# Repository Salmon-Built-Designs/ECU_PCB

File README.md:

# ECU_PCB
PCB layout designed wiht Eagle 8.6.0 Free version. This PCB is designed as a shield for Arduino Mega 2560 R3 for the Engine Control Unit project

The routing is single layered. There are several options of routing, but only one served in this repository

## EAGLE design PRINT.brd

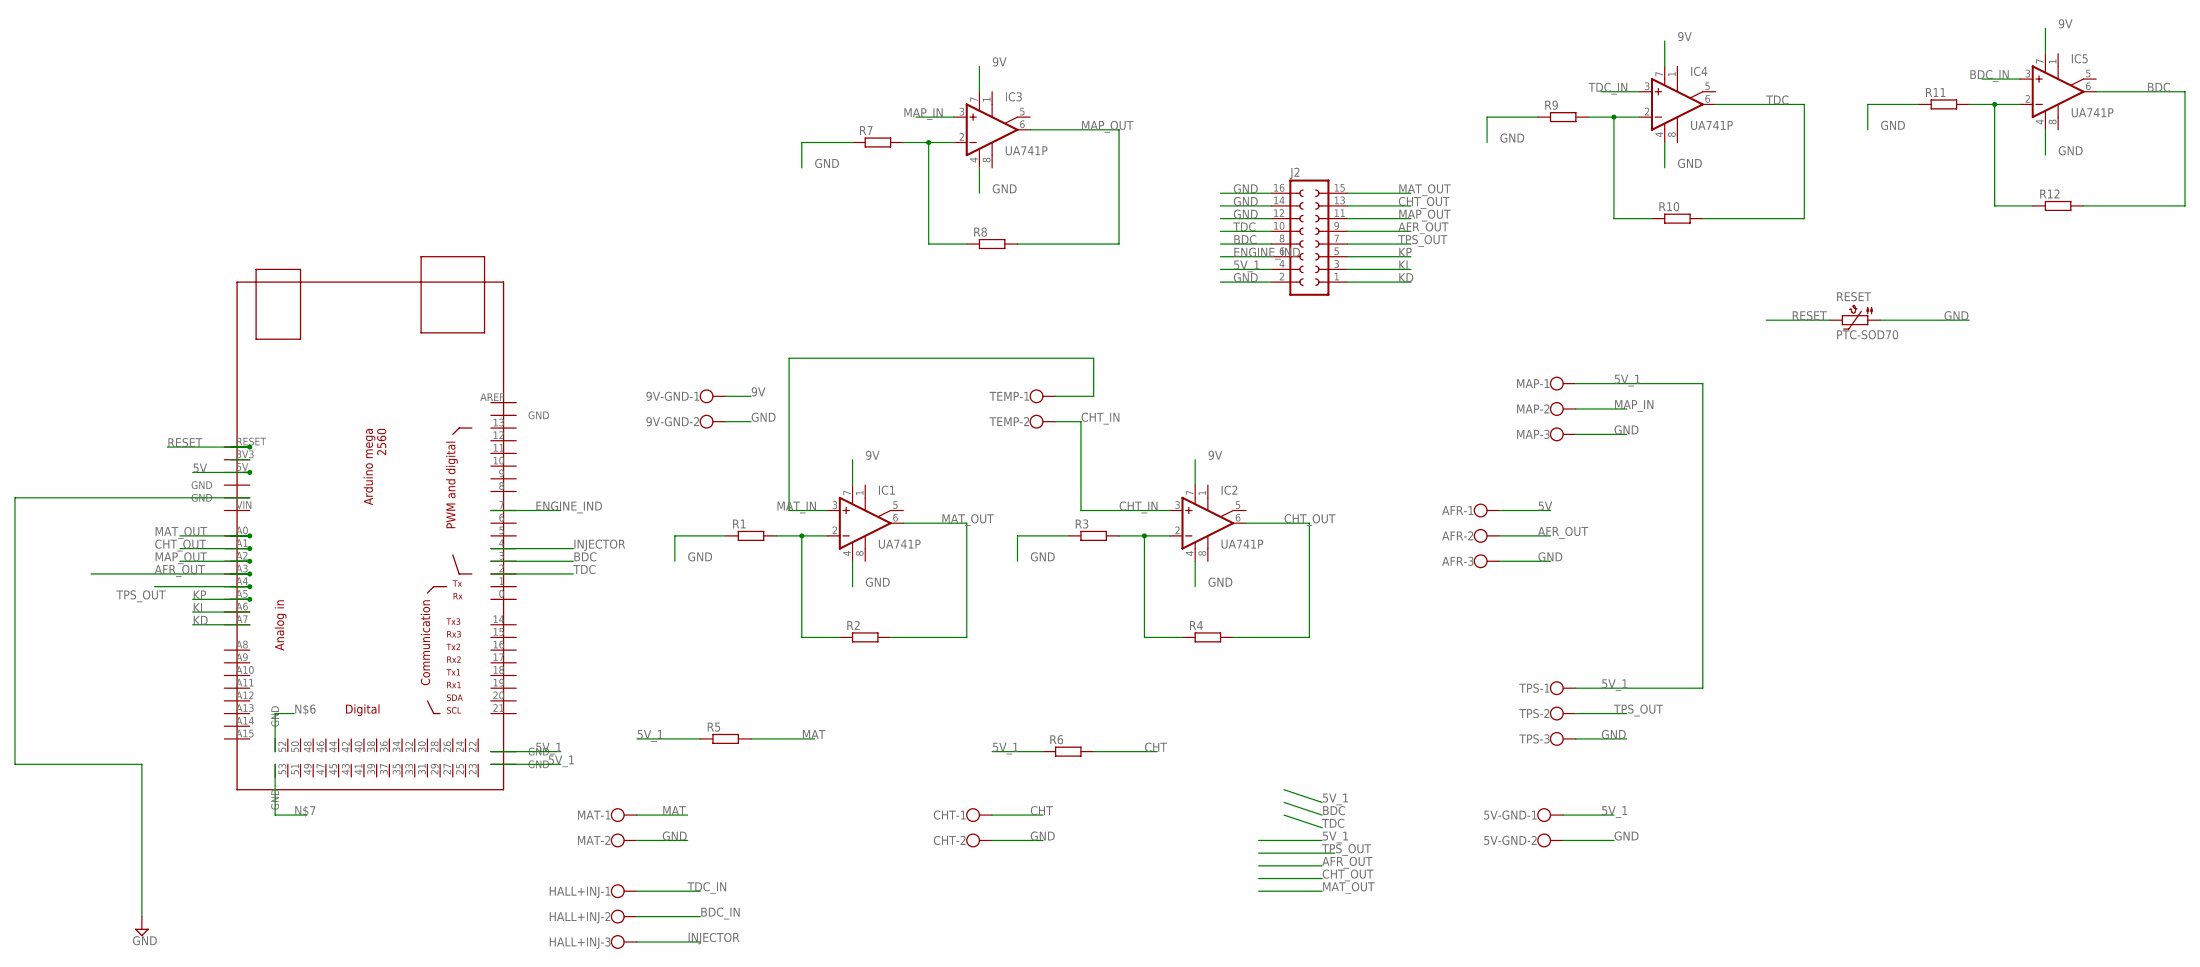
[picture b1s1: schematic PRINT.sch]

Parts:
5V-GND, 9V-GND: W237-102
AFR: W237-103
CHT: W237-102
HALL+INJ: W237-103
IC1, IC2, IC3, IC4, IC5: UA741P; DIL08
J2: SOCKET-16V; S16V
MAP: W237-103
MAT: W237-102
R1, R2, R3, R4, R5, R6, R7, R8, R9, R10, R11, R12: R0204/7; 0204/7
RESET: PTC-SOD70; SOD70
TEMP: W237-102
TPS: W237-103
U$1: MEGA_DEVICE; MEGAOUTLINE

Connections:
5V: AFR.1, U$1.5V
5V_1: 5V-GND.1, J2.4, MAP.1, R5.1, R6.1, TPS.1, U$1.GND@4 (GND), U$1.GND@5 (GND)
9V: 9V-GND.1, IC1.7 (V+), IC2.7 (V+), IC3.7 (V+), IC4.7 (V+), IC5.7 (V+)
AFR_OUT: AFR.2, J2.9, U$1.A3
BDC: IC5.6 (OUT), J2.8, R12.2, U$1.3
BDC_IN: HALL+INJ.2, IC5.3 (+IN)
CHT: CHT.1, R6.2
CHT_IN: IC2.3 (+IN), TEMP.2
CHT_OUT: IC2.6 (OUT), J2.13, R4.2, U$1.A1
ENGINE_IND: J2.6, U$1.7
GND: 5V-GND.2, 9V-GND.2, AFR.3, CHT.2, IC1.4 (V-), IC2.4 (V-), IC3.4 (V-), IC4.4 (V-), IC5.4 (V-), J2.2, J2.12, J2.14, J2.16, MAP.3, MAT.2, R1.1, R3.1, R7.1, R9.1, R11.1, RESET.1, TPS.3, U$1.GND@3 (GND)
INJECTOR: HALL+INJ.3, U$1.4
KD: J2.1, U$1.A7
KI: J2.3, U$1.A6
KP: J2.5, U$1.A5
MAP_IN: IC3.3 (+IN), MAP.2
MAP_OUT: IC3.6 (OUT), J2.11, R8.2, U$1.A2
MAT: MAT.1, R5.2
MAT_IN: IC1.3 (+IN), TEMP.1
MAT_OUT: IC1.6 (OUT), J2.15, R2.2, U$1.A0
unnamed: IC1.2 (-IN), R1.2, R2.1
unnamed: IC2.2 (-IN), R3.2, R4.1
unnamed: IC3.2 (-IN), R7.2, R8.1
unnamed: IC4.2 (-IN), R9.2, R10.1
unnamed: IC5.2 (-IN), R11.2, R12.1
RESET: RESET.2, U$1.RESET
TDC: IC4.6 (OUT), J2.10, R10.2, U$1.2
TDC_IN: HALL+INJ.1, IC4.3 (+IN)
TPS_OUT: J2.7, TPS.2, U$1.A4

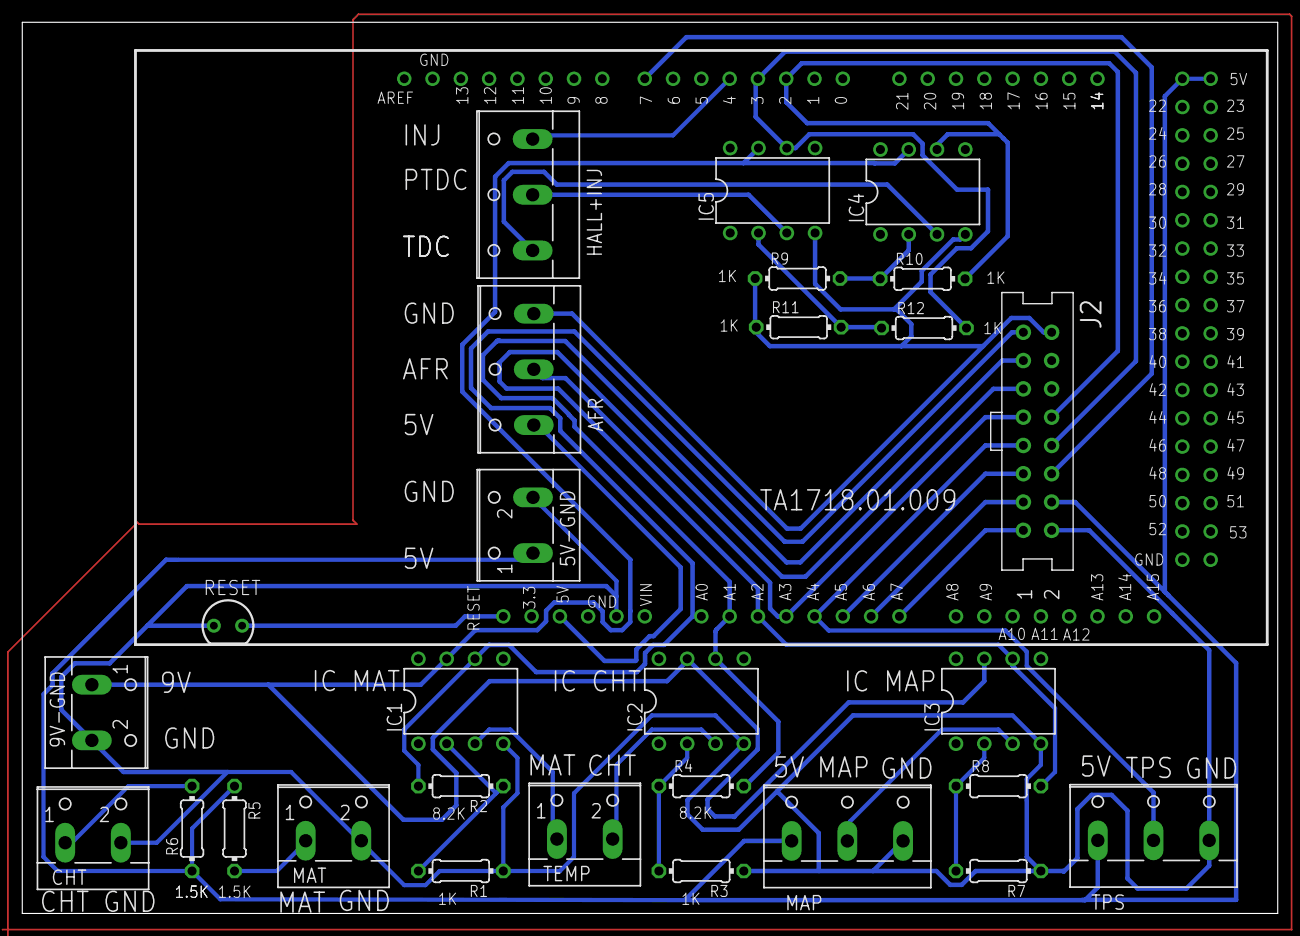
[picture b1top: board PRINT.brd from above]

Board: 2 copper layers, 112.7 x 80.0 mm, 29 parts (0 on the bottom side), 29 nets.

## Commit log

2018-05-29 PCB designed with eagle
